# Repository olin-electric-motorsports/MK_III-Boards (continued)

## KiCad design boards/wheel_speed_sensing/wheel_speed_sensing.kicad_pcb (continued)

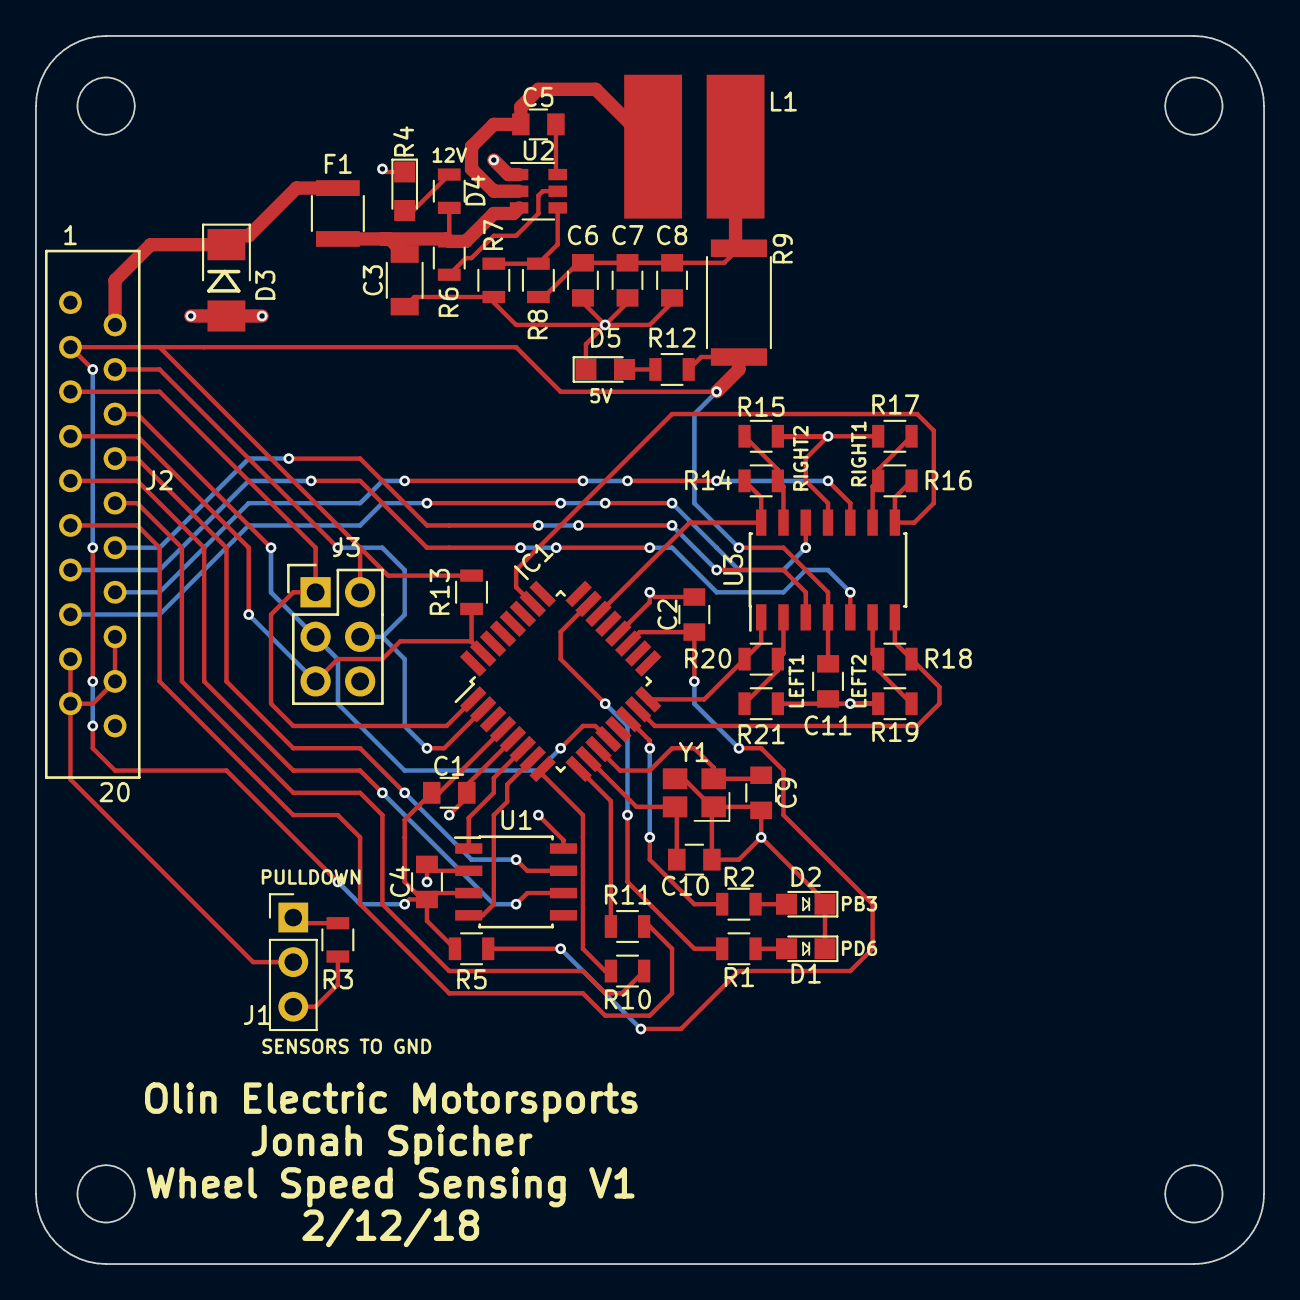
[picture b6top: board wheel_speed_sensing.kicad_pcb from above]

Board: 2 copper layers, 70.0 x 70.0 mm, 47 parts (0 on the bottom side), 44 nets.

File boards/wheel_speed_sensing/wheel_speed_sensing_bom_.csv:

Component,Description,Part,References,Value,Footprint,Quantity Per PCB,Datasheet,Package,MPN,MFN,PurchasingLink
1,Cap 50V 0.1uF 10% 0805,C_0.1uF,C1 C4 C5,C_0.1uF,C_0805,3,http://datasheets.avx.com/X7RDielectric.pdf,Value,478-3352-1-ND,Digi-Key,https://www.digikey.com/products/en?keywords=478-3352-1-ND
2,Cap 50V 0.1uF 10% 0805,C_0.1uF,C8 C11,C_0.1uF,C_0805_OEM,2,http://datasheets.avx.com/X7RDielectric.pdf,Value,478-3352-1-ND,Digi-Key,https://www.digikey.com/products/en?keywords=478-3352-1-ND
3,Cap 50V 100pF 5% 0805,C_100pF,C2,C_100pF,C_0805,1,https://content.kemet.com/datasheets/KEM_C1003_C0G_SMD.pdf,Value,399-1122-1-ND,Digi-Key,https://www.digikey.com/product-detail/en/kemet/C0805C101J5G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
4,CAP CER 1UF 25V X7R 0805,C_1uF,C7,C_1uF,C_0805_OEM,1,http://datasheets.avx.com/X7RDielectric.pdf,Value,478-10487-1-ND,Digi-Key,https://www.digikey.com/product-detail/en/avx-corporation/08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
5,Unpolarized capacitor,C_22uF,C3,C_22uF,C_1206,1,http://www.samsungsem.com/kr/support/product-search/mlcc/__i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,Value,1276-2725-1-ND,Digi-Key,https://www.digikey.com/products/en?keywords=1276-2725-1-ND
6,Cap 50V 30pF 5% 0805,C_30pF,C9 C10,C_30pF,C_0805,2,https://media.digikey.com/pdf/Data%20Sheets/Samsung%20PDFs/C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,Value,1276-1130-1-ND,Digi-Key,https://www.digikey.com/product-detail/en/samsung-electro-me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
7,CAP CER 47UF 6.3V X5R 0805,C_47uF,C6,C_47uF,C_0805,1,http://www.yuden.co.jp/productdata/catalog/en/mlcc_all_e.pdf,Value,587-4280-1-ND,Digi-Key,https://www.digikey.com/product-detail/en/taiyo-yuden/JMK212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
8,DIODE ZENER 18V 5W DO214AA,D_Zener_18V,D3,D_Zener_18V,DO-214AA,1,http://www.mccsemi.com/up_pdf/SMBJ5338B-SMBJ5388B(SMB).pdf,DO-214AA (SMB),SMBJ5355B-TPMSCT-ND,Digi-Key,https://www.digikey.com/products/en?keywords=SMBJ5355B-TPMSCT-ND
9,LED_0805,LED_0805,D1 D2,LED_0805,LED_0805_OEM,2,http://www.osram-os.com/Graphics/XPic9/00078860_0.pdf,Value,475-1410-1-ND,Digi-Key,https://www.digikey.com/products/en?keywords=475-1410-1-ND
10,LED_0805,LED_0805,D4 D5,LED_0805,LED_0805,2,http://www.osram-os.com/Graphics/XPic9/00078860_0.pdf,Value,475-1410-1-ND,Digi-Key,https://www.digikey.com/products/en?keywords=475-1410-1-ND
11,PTC Fuse 16V 500mA,F_500mA_16V,F1,500mA,Fuse_1210,1,https://belfuse.com/resources/CircuitProtection/datasheets/0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,Value,507-1786-1-ND,Digi-Key,https://www.digikey.com/product-detail/en/bel-fuse-inc/0ZCH0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
12,"TQFP32, 16k Flash, 1k SRAM, 512B EEPROM, CAN",ATMEGA16M1,IC1,ATMEGA16M1,TQFP-32_7x7mm_Pitch0.8mm,1,http://www.atmel.com/Images/Atmel-8209-8-bit%20AVR%20ATmega1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,Value,ATMEGA16M1-AU-ND,Digi-Key,https://www.digikey.com/product-detail/en/atmel/ATMEGA16M1-A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
13,"Connector, double row, 02x03",CONN_02X03,J3,CONN_02X03,Pin_Header_Straight_2x03,1,http://portal.fciconnect.com/Comergent//fci/drawing/67996.pdf,Value,609-3234-ND,Digi-Key,https://www.digikey.com/product-detail/en/amphenol-fci/67997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
14,"Generic connector, single row, 01x03",Conn_01x03,J1,Conn_01x03,Pin_Header_Straight_1x03_Pitch2.54mm,1,,,,,
15,connector micromatch female RA 20,micromatch_female_RA_20,J2,micromatch_female_RA_20,micromatch_female_ra_20,1,,Value,A99490CT-ND,Digi-Key,https://www.digikey.com/product-detail/en/te-connectivity-am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
16,Inductor 4.7uH 4.4A,L_4.7uH,L1,L_4.7uH,4.7uH_Inductor_OEM,1,https://product.tdk.com/info/en/documents/wdcatalog/withdraw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,Value,445-6583-1-ND,Digi-Key,https://www.digikey.com/product-detail/en/tdk-corporation/VL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
17,Res 0 2512 3W Jumper,R_0_Jumper,R9,R_0_Jumper,R_2512,1,http://www.te.com/commerce/DocumentDelivery/DDEController?Ac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,Value,A121322CT-ND,Digi-Key,https://www.digikey.com/products/en?keywords=A121322CT-ND
18,Res 100 1%,R_100,R5,R_100,R_0805,1,https://www.seielect.com/Catalog/SEI-rncp.pdf,Value,RNCP0805FTD100RCT-ND,Digi-Key,https://www.digikey.com/products/en?keywords=RNCP0805FTD100RCT-ND
19,Res 10k 1%,R_10k,R6 R7 R13,R_10k,R_0805,3,http://www.bourns.com/data/global/pdfs/CRS.pdf,Value,CRS0805-FX-1002ELFCT-ND,Digi-Key,https://www.digikey.com/products/en?keywords=CRS0805-FX-1002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
20,Res 10k 1%,R_10k,R3,R_10k,R_0805_OEM,1,http://www.bourns.com/data/global/pdfs/CRS.pdf,Value,CRS0805-FX-1002ELFCT-ND,Digi-Key,https://www.digikey.com/products/en?keywords=CRS0805-FX-1002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
21,Res 1k 1%,R_1k,R4,R_1k,R_0805,1,https://www.seielect.com/Catalog/SEI-rncp.pdf,Value,RNCP0805FTD1K00CT-ND,Digi-Key,https://www.digikey.com/products/en?keywords=RNCP0805FTD1K00CT-ND
22,Res 200 5%,R_200,R1 R2 R10 R11,R_200,R_0805_OEM,4,https://www.seielect.com/Catalog/SEI-RMCF_RMCP.pdf,Value,RMCF0805JT200RCT-ND,Digi-Key,https://www.digikey.com/products/en?keywords=RMCF0805JT200RCT-ND
23,Res 200 5%,R_200,R12,R_200,R_0805,1,https://www.seielect.com/Catalog/SEI-RMCF_RMCP.pdf,Value,RMCF0805JT200RCT-ND,Digi-Key,https://www.digikey.com/products/en?keywords=RMCF0805JT200RCT-ND
24,RES SMD 330 OHM 1% 1/8W 0805,R_330,R15 R17 R19 R21,R_330,R_0805_OEM,4,https://www.seielect.com/Catalog/SEI-RMCF_RMCP.pdf,Value,RMCF0805FT330RCT-ND,Digi-Key,https://www.digikey.com/product-detail/en/stackpole-electron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
25,Res 3k 1% 0805 1/8W,R_3k,R14 R16 R18 R20,R_3k,R_0805_OEM,4,https://www.seielect.com/Catalog/SEI-RMCF_RMCP.pdf,Value,RMCF0805FT3K00CT-ND,Digi-Key,https://www.digikey.com/product-detail/en/stackpole-electron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
26,Res 55.1k 1%,R_55.1k,R8,R_55.1k,R_0805,1,http://www.yageo.com.tw/exep/pages/download/literatures/PYu-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,Value,311-51.1KCRCT-ND,Digi-Key,https://www.digikey.com/products/en?keywords=311-51.1KCRCT-ND
27,"High-Speed CAN Transceiver, 1Mbps, 5V supply, SPLIT pin, -40C to +125C, SOIC8 package",CAN_Transceiver,U1,CAN_Transceiver,SOIC-8_3.9x4.9mm_Pitch1.27mm,1,http://www.microchip.com/mymicrochip/filehandler.aspx?ddocna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,Value,MCP2561-E/SN-ND,Digi-Key,https://www.digikey.com/products/en?keywords=mcp2561-e%2Fsn
28,"Four channel Op-Amp, General Purpose, 1.3 MHz, 14-SOIC",LM324DT,U3,LM324DT,SOIC-14_3.9x8.7mm_Pitch1.27mm,1,http://www.st.com/content/ccc/resource/technical/document/da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,Value,497-1580-1-ND,Digi-Key,https://www.digikey.com/product-detail/en/stmicroelectronics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
29,4.5V - 17V Input 1A Synchronous Buck Converter,TPS561201,U2,TPS561201,SOT-23-6,1,http://www.ti.com/lit/ds/symlink/tps561201.pdf,Value,TPS561201,Digi-Key,https://www.digikey.com/products/en?keywords=296-46928-1-ND
30,"Two pin crystal, two ground/package pins (pin2 and 3) small symbol",Crystal_SMD,Y1,Crystal_SMD,Crystal_SMD_FA238,1,https://support.epson.biz/td/api/doc_check.php?dl=brief_FA-2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,Value,SER3686CT-ND,Digi-Key,https://www.digikey.com/products/en?keywords=SER3686CT-ND





Component Groups:,30
Component Count:,47
Fitted Components:,47
Number of PCBs:,1
Total components:,47
Schematic Version:,
Schematic Date:,
BoM Date:,Mon 12 Feb 2018 09:51:14 PM EST
Schematic Source:,/home/jonah/Desktop/Formula/MK_III-Boards/boards/wheel_speed_sensing/wheel_speed_sensing.sch
KiCad Version:,Eeschema 4.0.7-e2-6376~58~ubuntu16.04.1
